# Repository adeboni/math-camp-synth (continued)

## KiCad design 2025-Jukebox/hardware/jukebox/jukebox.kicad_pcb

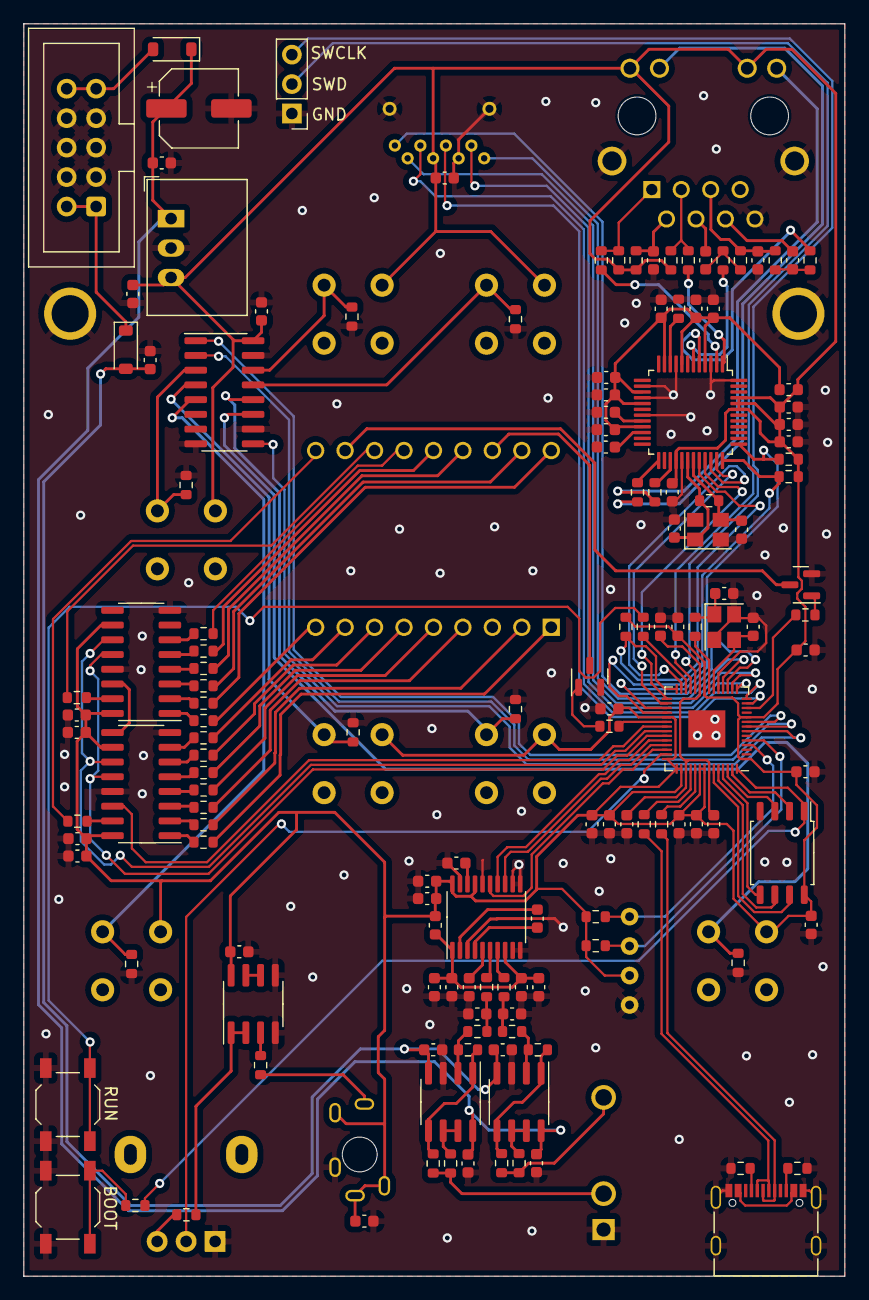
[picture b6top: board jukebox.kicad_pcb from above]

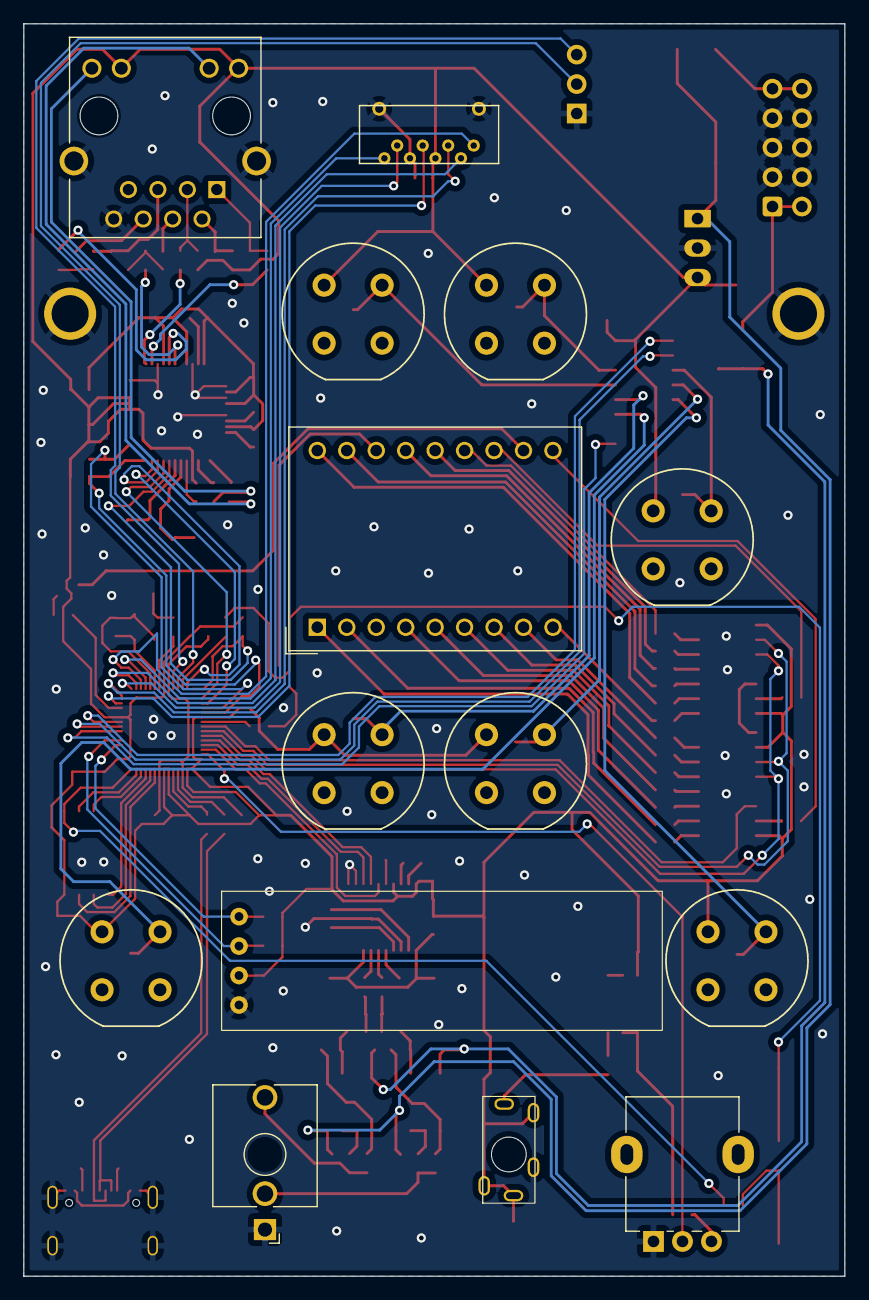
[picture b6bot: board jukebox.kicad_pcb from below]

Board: 2 copper layers, 70.8 x 108.0 mm, 160 parts (14 on the bottom side), 140 nets.

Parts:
C1, C2, C3, C4, C5, C6, C7, C8, C9, C13, C14, C15, C16, C17, C18, C19, C20, C21, C22, C23, C27, C31, C38, C40, C45, C46, C53, C54, C55, C56, C57, C59: 100n; C_0603_1608Metric
C10, C11, C44: 1u; C_0603_1608Metric
C12, C30, C36, C37, C39, C41, C42, C47, C48, C52, C58: 10u; C_0603_1608Metric
C24, C28: 27p; C_0603_1608Metric
C25, C29: 22p; C_0603_1608Metric
C26, C32: 10n; C_0603_1608Metric
C33, C34: 6.8n; C_0603_1608Metric
C35: 100u; CP_Elec_6.3x5.4
C43, C49: 2.2u; C_0603_1608Metric
C50, C51: 2.2n; C_0603_1608Metric
D1, D2: SM4007; D_SOD-123
FB1, FB3: FerriteBead; L_0603_1608Metric
H1, H2: MountingHole_Pad; MountingHole_3.2mm_M3_DIN965_Pad
J1: AudioJack3_SwitchTR; STX-3790-5N
J2: USB_C_Receptacle_USB2.0; USB_C_Receptacle_Palconn_UTC16-G
J3: AudioJack2_SwitchT; Jack_3.5mm_QingPu_WQP-PJ398SM_Vertical_CircularHoles
J4: SI-46001-F; BEL_SI-46001-F
J5: Conn_01x04; SSD1306
J6: Conn_02x05_Odd_Even; IDC-Header_2x05_P2.54mm_Vertical
J7: Conn_01x03; PinHeader_1x03_P2.54mm_Vertical
Q1, Q2: MMBT3904; SOT-23
R1, R2, R24, R25, R38: 1k; R_0603_1608Metric
R3, R6, R13, R17, R18, R28, R31, R32, R33, R35, R36, R37, R39, R40, R41, R58: 100; R_0603_1608Metric
R4, R5: 27; R_0603_1608Metric
R7, R10, R59, R61: 5.1k; R_0603_1608Metric
R8, R14, R16, R43, R44, R45, R46, R47, R48, R49, R50, R51, R54, R55: 10k; R_0603_1608Metric
R9, R11, R12, R15: 4.7; R_0603_1608Metric
R19, R20, R21, R22: 49.9; R_0603_1608Metric
R23: 1M; R_0603_1608Metric
R26, R27, R34, R42: 470; R_0603_1608Metric
R29: 12.4k; R_0603_1608Metric
R30: 10; R_0603_1608Metric
R52, R53, R56, R57: 75; R_0603_1608Metric
R60: 100k; R_0603_1608Metric
RV1: 100k; Potentiometer_Alpha_RD901F-40-00D_Single_Vertical
SW1, SW2: SW_Push; SW_SPST_TL3342
SW3, SW4, SW5, SW6, SW7, SW8, SW9: SW_Push; Push_E-Switch_KS01Q01
U1: PCM5100A; TSSOP-20_4.4x6.5mm_P0.65mm
U2: RP2040; QFN-56-1EP_7x7mm_P0.4mm_EP3.2x3.2mm
U3: W5500; LQFP-48_7x7mm_P0.5mm
U4: PDC54-11GWA; DA56-11CGKWA
U5, U8: 74HC595; SOIC-16_3.9x9.9mm_P1.27mm
U6: R-783.3-1.0; Converter_DCDC_RECOM_R-78E-0.5_THT
U7: W25Q128JVS; SOIC-8_5.23x5.23mm_P1.27mm
U9: PJS008U-3000-0
U10, U11: NE5532; SOIC-8_3.9x4.9mm_P1.27mm
U12: MCP6002-xSN; SOIC-8_3.9x4.9mm_P1.27mm
U13: 74HC165; SOIC-16_3.9x9.9mm_P1.27mm
Y1: 12MHz; Crystal_SMD_3225-4Pin_3.2x2.5mm
Y2: 25MHz; Crystal_SMD_3225-4Pin_3.2x2.5mm

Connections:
+1V1: C1.1, C2.1, C10.1, U2.23 (DVDD), U2.45 (VREG_VOUT), U2.50 (DVDD)
+3.3V: C3.1, C4.1, C5.1, C6.1, C7.1, C8.1, C9.1, C11.1, C12.1, C13.1, C14.1, C15.1, C16.1, C23.1, C27.1, C36.1, C37.1, C38.1, C39.1, C40.1, C42.1, C57.1, C58.1, C59.1, FB1.1, FB3.1, J1.R, J1.RN, J1.TN, J4.10, J4.12, J5.3, R8.1, R14.1, R16.1, R19.2, R20.2, R30.2, R59.2, R61.2, SW3.1, SW4.1, SW5.1, SW6.1, SW7.1, SW8.1, SW9.1, U1.17 (XSMT), U1.20 (DVDD), U2.1 (IOVDD), U2.10 (IOVDD), U2.22 (IOVDD), U2.33 (IOVDD), U2.42 (IOVDD), U2.43 (ADC_AVDD), U2.44 (VREG_IN), U2.48 (USB_VDD), U2.49 (IOVDD), U3.28 (VDD), U3.43 (PMODE2), U3.44 (PMODE1), U3.45 (PMODE0), U5.10 (~SRCLR), U5.16 (VCC), U6.3 (OUT), U7.8 (VCC), U8.10 (~SRCLR), U8.16 (VCC), U9.P$4 (4_VDD), U12.8 (V+), U13.16 (VCC)
+3.3VA: C17.1, C18.1, C19.1, C20.1, C21.1, C22.1, FB1.2, U3.4 (AVDD), U3.8 (AVDD), U3.11 (AVDD), U3.15 (AVDD), U3.17 (AVDD), U3.21 (AVDD)
+12V: C35.1, C41.1, C53.1, C55.1, D2.1 (K), U6.1 (IN), U10.8 (V+), U11.8 (V+)
-12V: C52.1, C54.2, C56.2, D1.2 (A), U10.4 (V-), U11.4 (V-)
/CS_0: R8.2, U2.28 (GPIO17), U3.32 (~SCS)
/INTn: R14.2, U2.32 (GPIO21), U3.36 (~INT)
/MISO_0: U2.27 (GPIO16), U3.34 (MISO)
/MOSI_0: U2.30 (GPIO19), U3.35 (MOSI)
/QSPI_SCLK: U2.52 (QSPI_SCLK), U7.6 (CLK)
/QSPI_SD0: U2.53 (QSPI_SD0), U7.5 (DI(IO0))
/QSPI_SD1: U2.55 (QSPI_SD1), U7.2 (DO(IO1))
/QSPI_SD2: U2.54 (QSPI_SD2), U7.3 (IO2)
/QSPI_SD3: U2.51 (QSPI_SD3), U7.7 (IO3)
/QSPI_SS: R38.1, U2.56 (QSPI_SS), U7.1 (~CS)
/RSTn: R16.2, U2.31 (GPIO20), U3.37 (~RST)
/RUN: R25.1, U2.26 (RUN)
/SCK_0: U2.29 (GPIO18), U3.33 (SCLK)
/~USB_BOOT: R38.2, SW2.2
ACTn: R27.1, U3.27 (ACTLED)
BCK_PWM1: U1.13 (BCK), U2.39 (GPIO27_ADC1)
BTN_CP: U2.8 (GPIO6), U13.2 (CP)
BTN_PL: U2.9 (GPIO7), U13.1 (~PL)
BTN_Q7: U2.7 (GPIO5), U13.9 (Q7)
D+: J2.A6 (D+), J2.B6 (D+), R4.1
D-: J2.A7 (D-), J2.B7 (D-), R5.1
GND: C1.2, C2.2, C3.2, C4.2, C5.2, C6.2, C7.2, C8.2, C9.2, C10.2, C11.2, C12.2, C13.2, C14.2, C15.2, C16.2, C17.2, C18.2, C19.2, C20.2, C21.2, C22.2, C23.2, C24.2, C25.1, C26.1, C27.2, C28.2, C29.2, C30.2, C31.2, C32.1, C35.2, C36.2, C37.2, C38.2, C39.2, C40.2, C41.2, C42.2, C44.2, C45.2, C46.2, C47.2, C48.2, C49.2, C50.2, C51.1, C52.2, C53.2, C54.1, C55.2, C56.1, C57.2, C58.2, C59.2, H1.1, H2.1, J1.S, J2.A1 (GND), J2.A12 (GND), J2.B1 (GND), J2.B12 (GND), J2.S1 (SHIELD), J3.S, J4.8, J4.SH, J5.4, J6.3, J6.4, J6.5, J6.6, J6.7, J6.8, J7.1, Q1.2 (E), Q2.2 (E), R7.1, R10.1, R29.1, R43.2, R44.2, R45.2, R46.2, R47.2, R48.2, R49.2, RV1.1, SW1.1, SW2.1, U1.3 (CPGND), U1.9 (AGND), U1.10 (DEMP), U1.11 (FLT), U1.12 (SCK), U1.16 (FMT), U1.19 (DGND), U2.19 (TESTEN), U2.57 (GND), U3.3 (AGND), U3.9 (AGND), U3.14 (AGND), U3.16 (AGND), U3.19 (AGND), U3.29 (GND), U3.48 (AGND), U5.8 (GND), U5.13 (~OE), U6.2 (GND), U7.4 (GND), U8.8 (GND), U8.13 (~OE), U9.P$6 (6_VSS/GND), U9.P$9 (HOUSING_1), U9.P$10 (HOUSING_2), U10.3 (+), U11.3 (+), U12.4 (V-), U12.5 (+), U13.8 (GND), U13.10 (DS), U13.15 (~CE), Y1.2, Y1.4, Y2.2, Y2.4
LINKn: R26.1, U3.25 (LINKLED)
LRCLK_PWM0: U1.15 (LRCK), U2.40 (GPIO28_ADC2)
NUM_A: R33.1, U4.12 (A)
NUM_B: R3.1, U4.10 (B)
NUM_C: R35.1, U4.9 (C)
NUM_D: R31.1, U4.7 (D)
NUM_DIG1: R1.2, U2.34 (GPIO22)
NUM_DIG2: R2.2, U2.12 (GPIO9)
NUM_DP: R32.1, U4.8 (DP)
NUM_E: R6.1, U4.1 (E)
NUM_EN: U2.37 (GPIO25), U5.12 (RCLK), U8.12 (RCLK)
NUM_F: R36.1, U4.18 (F)
NUM_G: R37.1, U4.17 (G)
NUM_H: R39.1, U4.15 (H)
NUM_J: R40.1, U4.14 (J)
NUM_K: R28.1, U4.6 (K)
NUM_L: R18.1, U4.5 (L)
NUM_M: R17.1, U4.4 (M)
NUM_N: R13.1, U4.2 (N)
NUM_P: R41.1, U4.13
NUM_SCK: U2.36 (GPIO24), U5.11 (SRCLK), U8.11 (SRCLK)
NUM_SER: U2.35 (GPIO23), U5.14 (SER)
unnamed: C28.1, R24.2, Y1.1
unnamed: C50.1, R42.2, R55.1
unnamed: C51.2, R34.2, R50.1
unnamed: D1.1 (K), J6.1, J6.2
unnamed: D2.2 (A), J6.9, J6.10
unnamed: J1.T, R60.1
unnamed: J2.A5 (CC1), R7.2
unnamed: J2.B5 (CC2), R10.2
unnamed: J2.A4 (VBUS), J2.A9 (VBUS), J2.B4 (VBUS), J2.B9 (VBUS)
unnamed: J3.T, R56.2, R57.2
unnamed: J3.TN, R52.2, R53.2
unnamed: J4.9, R27.2
unnamed: J4.11, R26.2
unnamed: C33.2, J4.4 (RD+)
unnamed: C34.1, J4.6 (RD-)
unnamed: C32.2, J4.2 (TCT), R30.1
unnamed: J7.2, U2.25 (SWD)
unnamed: J7.3, U2.24 (SWCLK)
unnamed: Q1.1 (B), R1.1
unnamed: Q1.3 (C), U4.16 (DIG_1)
unnamed: Q2.1 (B), R2.1
unnamed: Q2.3 (C), U4.11 (DIG_2)
unnamed: R25.2, SW1.2
unnamed: R58.2, RV1.3
unnamed: C43.2, U1.4 (CAPM)
unnamed: C43.1, U1.2 (CAPP)
unnamed: C44.1, U1.18 (LDOO)
unnamed: R34.1, U1.6 (OUTL)
unnamed: R42.1, U1.7 (OUTR)
unnamed: C49.1, U1.5 (VNEG)
unnamed: R5.2, U2.46 (USB_DM)
unnamed: R4.2, U2.47 (USB_DP)
unnamed: C24.1, U2.20 (XIN), Y1.3
unnamed: R24.1, U2.21 (XOUT)
unnamed: C31.1, U3.22 (1V2O)
unnamed: R29.2, U3.10 (EXRES1)
unnamed: R12.1, U3.5 (RXN)
unnamed: R15.2, U3.6 (RXP)
unnamed: C30.1, U3.20 (TOCAP)
unnamed: R9.1, U3.1 (TXN)
unnamed: R11.2, U3.2 (TXP)
unnamed: C25.2, R23.2, U3.30 (XI/CLKIN), Y2.1
unnamed: C29.1, R23.1, U3.31 (XO), Y2.3
unnamed: R3.2, U5.15 (QA)
unnamed: R6.2, U5.1 (QB)
unnamed: R13.2, U5.2 (QC)
unnamed: R17.2, U5.3 (QD)
unnamed: R18.2, U5.4 (QE)
unnamed: R28.2, U5.5 (QF)
unnamed: R31.2, U5.6 (QG)
unnamed: U5.9 (QH'), U8.14 (SER)
unnamed: R32.2, U5.7 (QH)
unnamed: R33.2, U8.15 (QA)
unnamed: R35.2, U8.1 (QB)
unnamed: R36.2, U8.2 (QC)
unnamed: R37.2, U8.3 (QD)
unnamed: R39.2, U8.4 (QE)
unnamed: R40.2, U8.5 (QF)
unnamed: R41.2, U8.6 (QG)
unnamed: R50.2, R51.1, U10.2 (-)
unnamed: R51.2, R53.1, U10.1, U10.5 (+)
unnamed: R52.1, U10.6 (-), U10.7
unnamed: R54.1, R55.2, U11.2 (-)
unnamed: R54.2, R57.1, U11.1, U11.5 (+)
unnamed: R56.1, U11.6 (-), U11.7
unnamed: R60.2, U12.3 (+)
unnamed: R58.1, U12.1, U12.2 (-)
unnamed: U12.6 (-), U12.7
unnamed: R49.1, SW3.2, U13.11 (D0)
unnamed: R48.1, SW6.2, U13.12 (D1)
unnamed: R47.1, SW4.2, U13.13 (D2)
unnamed: R46.1, SW5.2, U13.14 (D3)
unnamed: R45.1, SW8.2, U13.3 (D4)
unnamed: R44.1, SW7.2, U13.4 (D5)
unnamed: R43.1, SW9.2, U13.5 (D6)
PCM_DATA: U1.14 (DIN), U2.38 (GPIO26_ADC0)
RCT: C26.2, J4.5 (RCT), R21.2, R22.2
RXN: C34.2, R12.2, R21.1
RXP: C33.1, R15.1, R22.1
SCL: J5.2, R61.1, U2.5 (GPIO3)
SDA: J5.1, R59.1, U2.4 (GPIO2)
SD_CLK: U2.13 (GPIO10), U9.P$5 (5_CLK)
SD_CMD: U2.14 (GPIO11), U9.P$3 (3_CMD/DI)
SD_DAT0: U2.15 (GPIO12), U9.P$7 (7_DAT0/D0)
SD_DAT1: U2.18 (GPIO15), U9.P$8 (8_DAT1/X)
SD_DAT2: U2.17 (GPIO14), U9.P$1 (1_DAT2/X)
SD_DAT3: U2.16 (GPIO13), U9.P$2 (2_CD/DAT3/CS)
TXN: J4.3 (TD-), R9.2, R19.1
TXP: J4.1 (TD+), R11.1, R20.1
VOLUME: RV1.2, U2.41 (GPIO29_ADC3)
V_AUDIO: C45.1, C46.1, C47.1, C48.1, FB3.2, U1.1 (CPVDD), U1.8 (AVDD)

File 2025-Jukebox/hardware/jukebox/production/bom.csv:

Designator,Footprint,Quantity,Value,LCSC Part #
"C1, C13, C14, C15, C16, C17, C18, C19, C2, C20, C21, C22, C23, C27, C3, C31, C38, C4, C40, C45, C46, C5, C53, C54, C55, C56, C57, C59, C6, C7, C8, C9",0603,32,100n,C14663
"C10, C11, C44",0603,3,1u,C15849
"C12, C30, C36, C37, C39, C41, C42, C47, C48, C52, C58",0603,11,10u,C96446
"C24, C28",0603,2,27p,C1653
"C25, C29",0603,2,22p,C1653
"C26, C32",0603,2,10n,C57112
"C33, C34",0603,2,6.8n,C1631
C35,CP_Elec_6.3x5.4,1,100u,C180946
"C43, C49",0603,2,2.2u,C23630
"C50, C51",0603,2,2.2n,C1604
"D1, D2",D_SOD-123,2,SM4007,C64898
"FB1, FB3",0603,2,FerriteBead,C1002
J2,USB_C_Receptacle_Palconn_UTC16-G,1,USB_C_Receptacle_USB2.0,C709357
"Q1, Q2",SOT-23,2,MMBT3904,C20526
"R1, R2, R24, R25, R38",0603,5,1k,C21190
"R10, R59, R61, R7",0603,4,5.1k,C23186
"R11, R12, R15, R9",0603,4,4.7,C23164
"R13, R17, R18, R28, R3, R31, R32, R33, R35, R36, R37, R39, R40, R41, R58, R6",0603,16,100,C22775
"R14, R16, R43, R44, R45, R46, R47, R48, R49, R50, R51, R54, R55, R8",0603,14,10k,C25804
"R19, R20, R21, R22",0603,4,49.9,C23185
R23,0603,1,1M,C22935
"R26, R27, R34, R42",0603,4,470,C23179
R29,0603,1,12.4k,C22865
R30,0603,1,10,C22859
"R4, R5",0603,2,27,C25190
"R52, R53, R56, R57",0603,4,75,C4275
R60,0603,1,100k,C25803
"SW1, SW2",SW_SPST_TL3342,2,SW_Push,C318884
U1,TSSOP-20_4.4x6.5mm_P0.65mm,1,PCM5100A,C107671
"U10, U11",SOIC-8_3.9x4.9mm_P1.27mm,2,NE5532,C7426
U12,SOIC-8_3.9x4.9mm_P1.27mm,1,MCP6002-xSN,C7377
U13,SOIC-16_3.9x9.9mm_P1.27mm,1,74HC165,C5613
U2,QFN-56-1EP_7x7mm_P0.4mm_EP3.2x3.2mm,1,RP2040,C2040
U3,LQFP-48_7x7mm_P0.5mm,1,W5500,C32843
"U5, U8",SOIC-16_3.9x9.9mm_P1.27mm,2,74HC595,C5947
U7,SOIC-8_5.23x5.23mm_P1.27mm,1,W25Q128JVS,C97521
Y1,Crystal_SMD_3225-4Pin_3.2x2.5mm,1,12MHz,C9002
Y2,Crystal_SMD_3225-4Pin_3.2x2.5mm,1,25MHz,C9006

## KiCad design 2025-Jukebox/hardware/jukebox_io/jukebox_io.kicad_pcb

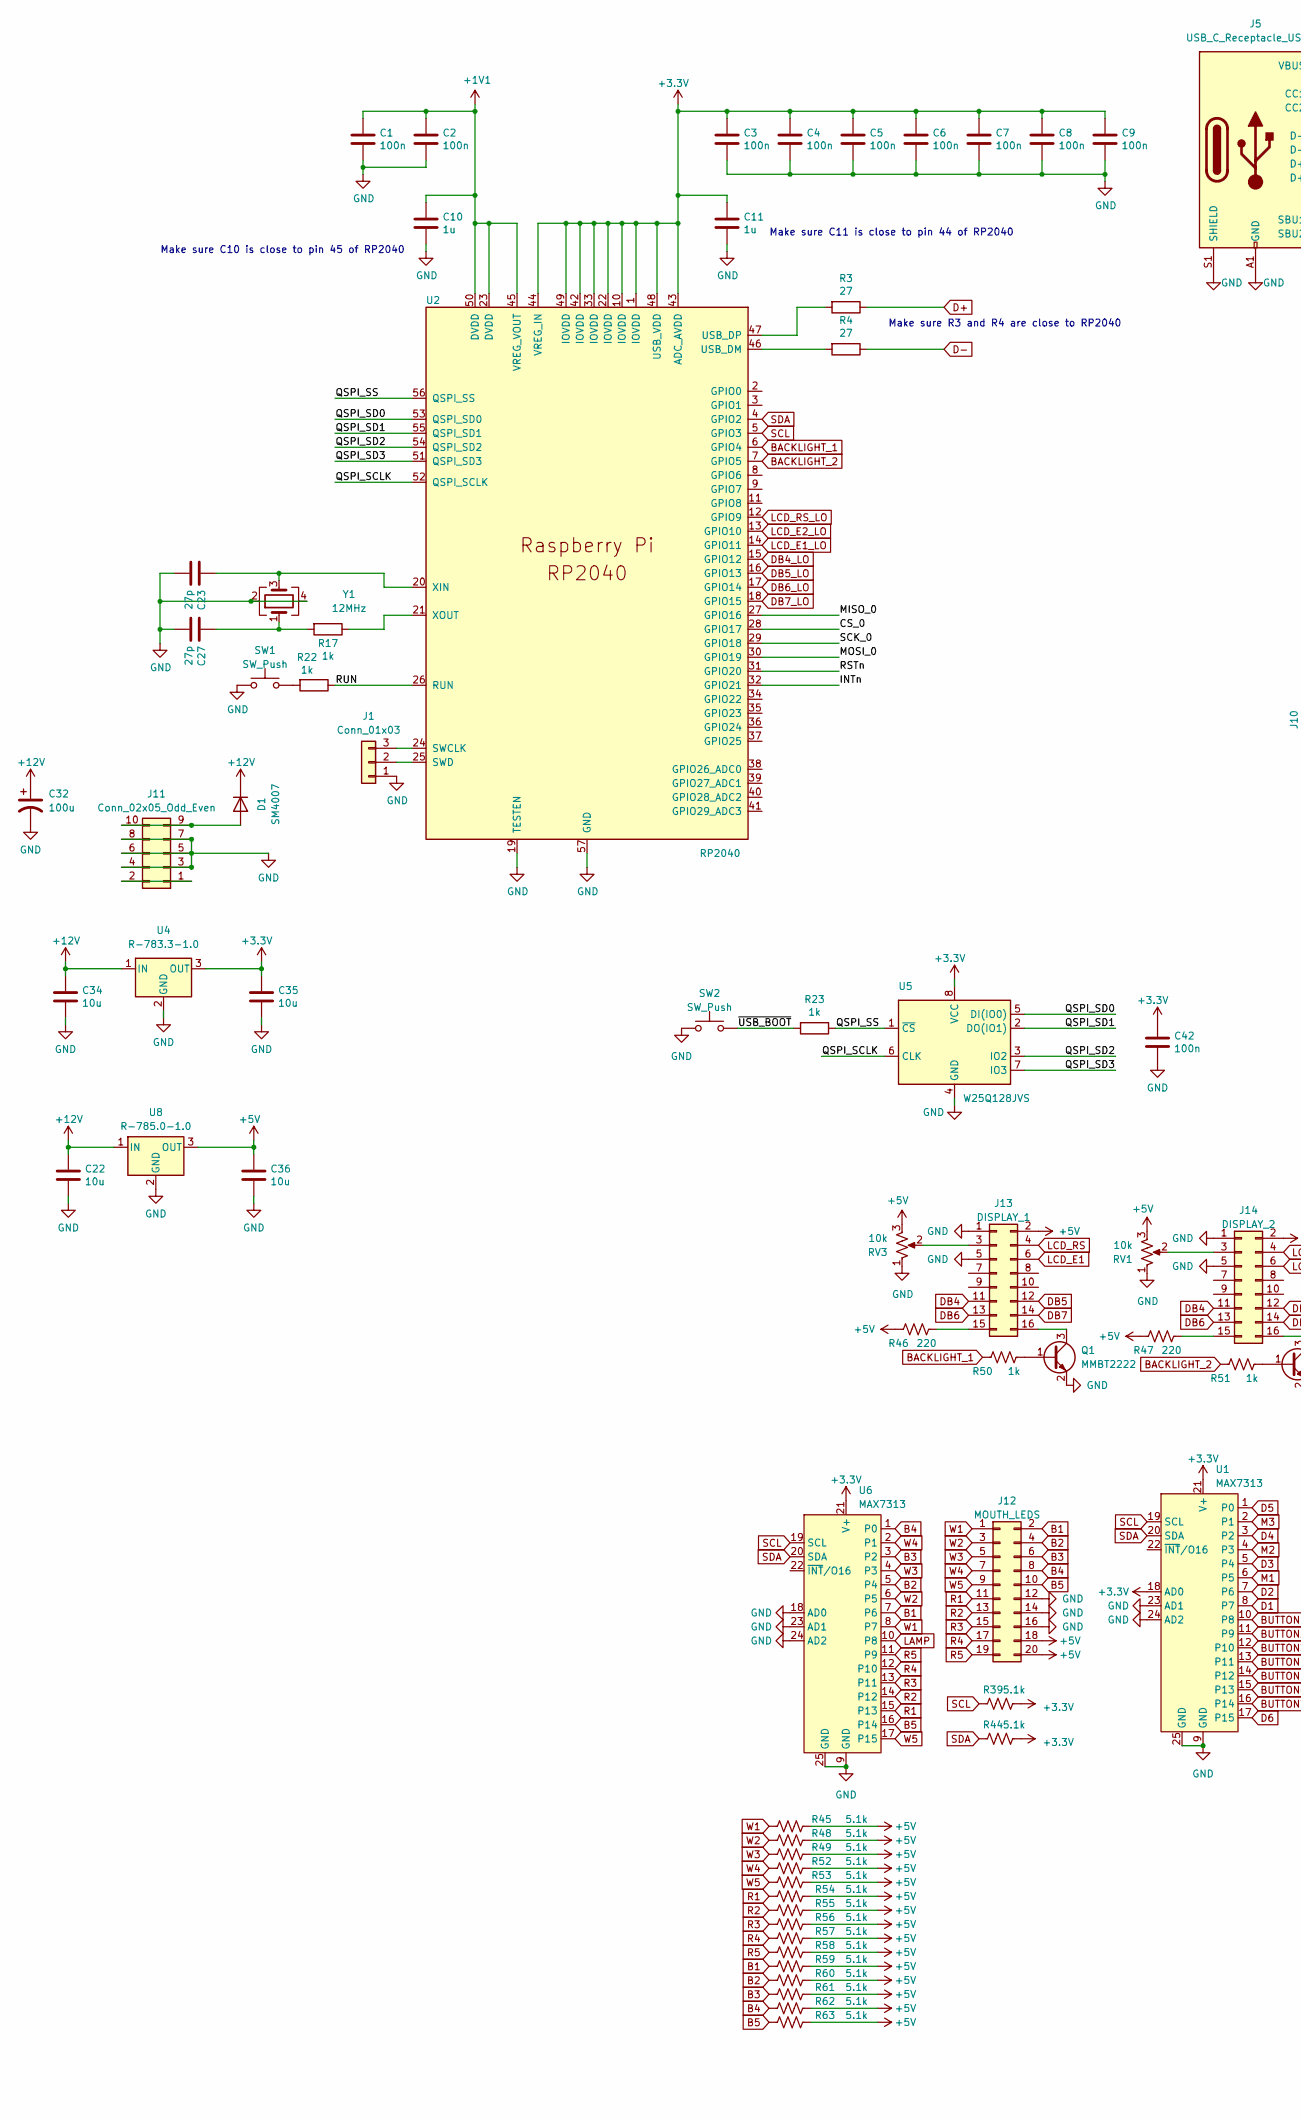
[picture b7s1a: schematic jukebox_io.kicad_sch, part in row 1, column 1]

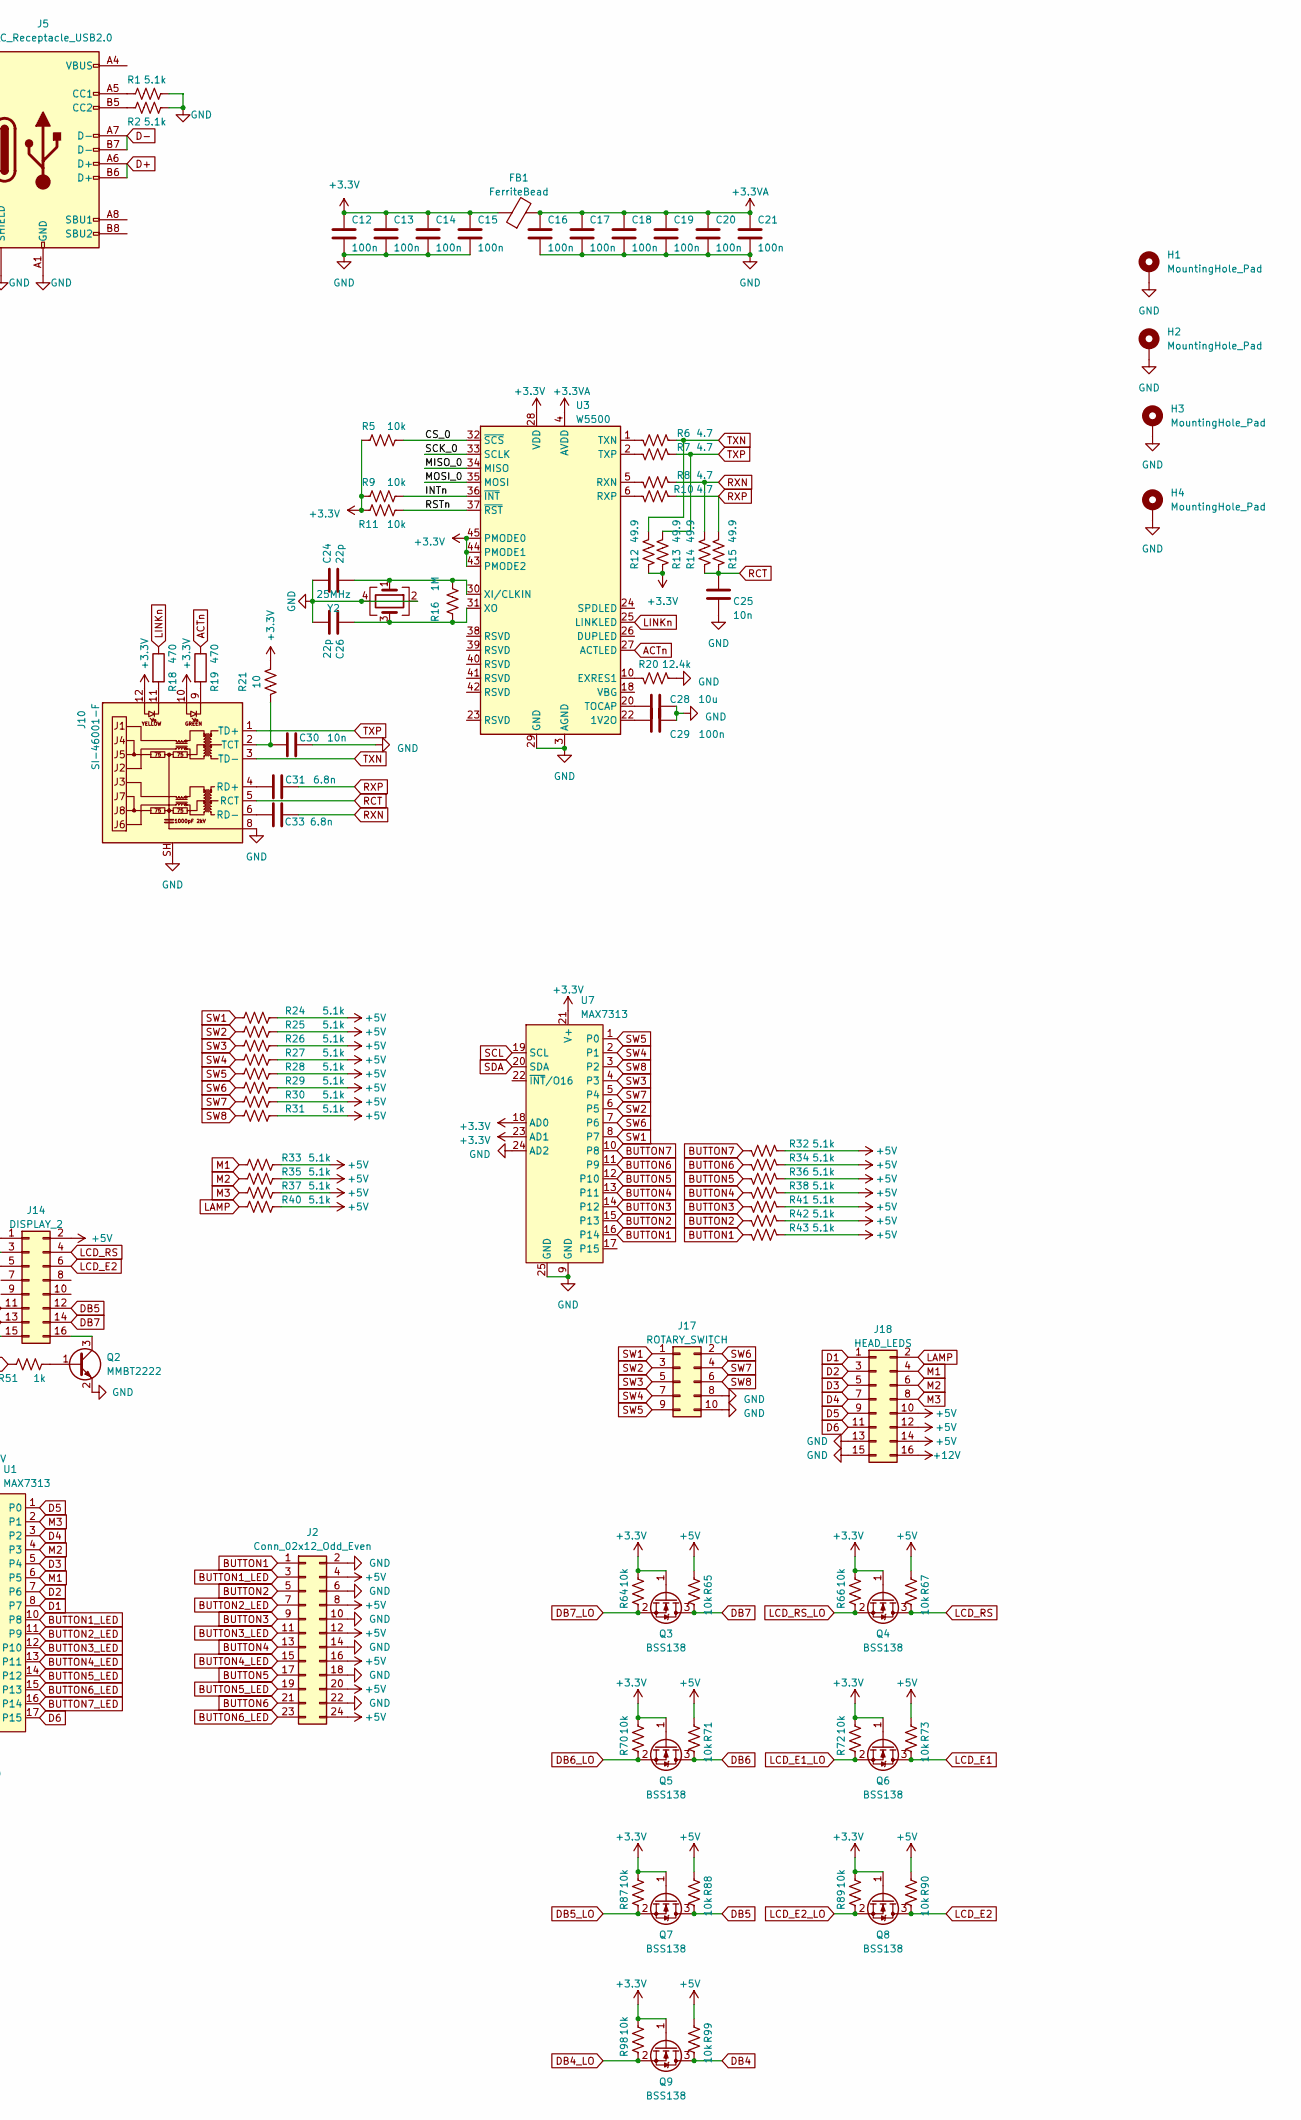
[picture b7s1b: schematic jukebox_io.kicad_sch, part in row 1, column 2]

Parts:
C1, C2, C3, C4, C5, C6, C7, C8, C9, C12, C13, C14, C15, C16, C17, C18, C19, C20, C21, C29, C42: 100n; C_0603_1608Metric
C10, C11: 1u; C_0603_1608Metric
C22, C28, C34, C35, C36: 10u; C_0603_1608Metric
C23, C27: 27p; C_0603_1608Metric
C24, C26: 22p; C_0603_1608Metric
C25, C30: 10n; C_0603_1608Metric
C31, C33: 6.8n; C_0603_1608Metric
C32: 100u; CP_Elec_6.3x5.4
D1: SM4007; D_SOD-123
FB1: FerriteBead; L_0603_1608Metric
H1, H2, H3, H4: MountingHole_Pad; MountingHole_3.2mm_M3_DIN965_Pad
J1: Conn_01x03; PinHeader_1x03_P2.54mm_Vertical
J2: Conn_02x12_Odd_Even; IDC-Header_2x12_P2.54mm_Vertical
J5: USB_C_Receptacle_USB2.0; USB_C_Receptacle_Palconn_UTC16-G
J10: SI-46001-F; BEL_SI-46001-F
J11: Conn_02x05_Odd_Even; IDC-Header_2x05_P2.54mm_Vertical
J12: MOUTH_LEDS; IDC-Header_2x10_P2.54mm_Vertical
J13: DISPLAY_1; IDC-Header_2x08_P2.54mm_Vertical
J14: DISPLAY_2; IDC-Header_2x08_P2.54mm_Vertical
J17: ROTARY_SWITCH; IDC-Header_2x05_P2.54mm_Vertical
J18: HEAD_LEDS; IDC-Header_2x08_P2.54mm_Vertical
Q1, Q2: MMBT2222; SOT-23
Q3, Q4, Q5, Q6, Q7, Q8, Q9: BSS138; SOT-23
R1, R2, R24, R25, R26, R27, R28, R29, R30, R31, R32, R33, R34, R35, R36, R37, R38, R39, R40, R41, R42, R43, R44, R45, R48, R49, R52, R53, R54, R55, R56, R57, R58, R59, R60, R61, R62, R63: 5.1k; R_0603_1608Metric
R3, R4: 27; R_0603_1608Metric
R5, R9, R11, R64, R65, R66, R67, R70, R71, R72, R73, R87, R88, R89, R90, R98, R99: 10k; R_0603_1608Metric
R6, R7, R8, R10: 4.7; R_0603_1608Metric
R12, R13, R14, R15: 49.9; R_0603_1608Metric
R16: 1M; R_0603_1608Metric
R17, R22, R23, R50, R51: 1k; R_0603_1608Metric
R18, R19: 470; R_0603_1608Metric
R20: 12.4k; R_0603_1608Metric
R21: 10; R_0603_1608Metric
R46, R47: 220; R_0603_1608Metric
RV1, RV3: 10k; Potentiometer_Bourns_3296W_Vertical
SW1, SW2: SW_Push; SW_SPST_TL3342
U1, U6, U7: MAX7313; TQFN-24-1EP_4x4mm_P0.5mm_EP2.6x2.6mm_ThermalVias
U2: RP2040; QFN-56-1EP_7x7mm_P0.4mm_EP3.2x3.2mm
U3: W5500; LQFP-48_7x7mm_P0.5mm
U4: R-783.3-1.0; Converter_DCDC_RECOM_R-78E-0.5_THT
U5: W25Q128JVS; SOIC-8_5.23x5.23mm_P1.27mm
U8: R-785.0-1.0; Converter_DCDC_RECOM_R-78E-0.5_THT
Y1: 12MHz; Crystal_SMD_3225-4Pin_3.2x2.5mm
Y2: 25MHz; Crystal_SMD_3225-4Pin_3.2x2.5mm

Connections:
+1V1: C1.1, C2.1, C10.1, U2.23 (DVDD), U2.45 (VREG_VOUT), U2.50 (DVDD)
+3.3V: C3.1, C4.1, C5.1, C6.1, C7.1, C8.1, C9.1, C11.1, C12.1, C13.1, C14.1, C15.1, C35.1, C42.1, FB1.1, J10.10, J10.12, Q3.1 (G), Q4.1 (G), Q5.1 (G), Q6.1 (G), Q7.1 (G), Q8.1 (G), Q9.1 (G), R5.1, R9.1, R11.1, R12.2, R13.2, R21.2, R39.2, R44.2, R64.2, R66.2, R70.2, R72.2, R87.2, R89.2, R98.2, U1.18 (AD0), U1.21 (V+), U2.1 (IOVDD), U2.10 (IOVDD), U2.22 (IOVDD), U2.33 (IOVDD), U2.42 (IOVDD), U2.43 (ADC_AVDD), U2.44 (VREG_IN), U2.48 (USB_VDD), U2.49 (IOVDD), U3.28 (VDD), U3.43 (PMODE2), U3.44 (PMODE1), U3.45 (PMODE0), U4.3 (OUT), U5.8 (VCC), U6.21 (V+), U7.18 (AD0), U7.21 (V+), U7.23 (AD1)
+3.3VA: C16.1, C17.1, C18.1, C19.1, C20.1, C21.1, FB1.2, U3.4 (AVDD), U3.8 (AVDD), U3.11 (AVDD), U3.15 (AVDD), U3.17 (AVDD), U3.21 (AVDD)
+5V: C36.1, J2.4, J2.8, J2.12, J2.16, J2.20, J2.24, J12.18, J12.20, J13.2, J14.2, J18.10, J18.12, J18.14, R24.2, R25.2, R26.2, R27.2, R28.2, R29.2, R30.2, R31.2, R32.2, R33.2, R34.2, R35.2, R36.2, R37.2, R38.2, R40.2, R41.2, R42.2, R43.2, R45.2, R46.1, R47.1, R48.2, R49.2, R52.2, R53.2, R54.2, R55.2, R56.2, R57.2, R58.2, R59.2, R60.2, R61.2, R62.2, R63.2, R65.1, R67.1, R71.1, R73.1, R88.1, R90.1, R99.1, RV1.3, RV3.3, U8.3 (OUT)
+12V: C22.1, C32.1, C34.1, D1.1 (K), J18.16, U4.1 (IN), U8.1 (IN)
/CS_0: R5.2, U2.28 (GPIO17), U3.32 (~SCS)
/INTn: R9.2, U2.32 (GPIO21), U3.36 (~INT)
/MISO_0: U2.27 (GPIO16), U3.34 (MISO)
/MOSI_0: U2.30 (GPIO19), U3.35 (MOSI)
/QSPI_SCLK: U2.52 (QSPI_SCLK), U5.6 (CLK)
/QSPI_SD0: U2.53 (QSPI_SD0), U5.5 (DI(IO0))
/QSPI_SD1: U2.55 (QSPI_SD1), U5.2 (DO(IO1))
/QSPI_SD2: U2.54 (QSPI_SD2), U5.3 (IO2)
/QSPI_SD3: U2.51 (QSPI_SD3), U5.7 (IO3)
/QSPI_SS: R23.1, U2.56 (QSPI_SS), U5.1 (~CS)
/RSTn: R11.2, U2.31 (GPIO20), U3.37 (~RST)
/RUN: R22.1, U2.26 (RUN)
/SCK_0: U2.29 (GPIO18), U3.33 (SCLK)
/~USB_BOOT: R23.2, SW2.2
ACTn: R19.1, U3.27 (ACTLED)
B1: J12.2, R59.1, U6.7 (P6)
B2: J12.4, R60.1, U6.5 (P4)
B3: J12.6, R61.1, U6.3 (P2)
B4: J12.8, R62.1, U6.1 (P0)
B5: J12.10, R63.1, U6.16 (P14)
BACKLIGHT_1: R50.1, U2.6 (GPIO4)
BACKLIGHT_2: R51.1, U2.7 (GPIO5)
BUTTON1: J2.1, R43.1, U7.16 (P14)
BUTTON1_LED: J2.3, U1.10 (P8)
BUTTON2: J2.5, R42.1, U7.15 (P13)
BUTTON2_LED: J2.7, U1.11 (P9)
BUTTON3: J2.9, R41.1, U7.14 (P12)
BUTTON3_LED: J2.11, U1.12 (P10)
BUTTON4: J2.13, R38.1, U7.13 (P11)
BUTTON4_LED: J2.15, U1.13 (P11)
BUTTON5: J2.17, R36.1, U7.12 (P10)
BUTTON5_LED: J2.19, U1.14 (P12)
BUTTON6: J2.21, R34.1, U7.11 (P9)
BUTTON6_LED: J2.23, U1.15 (P13)
BUTTON7: R32.1, U7.10 (P8)
BUTTON7_LED: U1.16 (P14)
D1: J18.1, U1.8 (P7)
D2: J18.3, U1.7 (P6)
D3: J18.5, U1.5 (P4)
D4: J18.7, U1.3 (P2)
D5: J18.9, U1.1 (P0)
D6: J18.11, U1.17 (P15)
D+: J5.A6 (D+), J5.B6 (D+), R3.1
D-: J5.A7 (D-), J5.B7 (D-), R4.1
DB4: J13.11, J14.11, Q9.3 (D), R99.2
DB4_LO: Q9.2 (S), R98.1, U2.15 (GPIO12)
DB5: J13.12, J14.12, Q7.3 (D), R88.2
DB5_LO: Q7.2 (S), R87.1, U2.16 (GPIO13)
DB6: J13.13, J14.13, Q5.3 (D), R71.2
DB6_LO: Q5.2 (S), R70.1, U2.17 (GPIO14)
DB7: J13.14, J14.14, Q3.3 (D), R65.2
DB7_LO: Q3.2 (S), R64.1, U2.18 (GPIO15)
GND: C1.2, C2.2, C3.2, C4.2, C5.2, C6.2, C7.2, C8.2, C9.2, C10.2, C11.2, C12.2, C13.2, C14.2, C15.2, C16.2, C17.2, C18.2, C19.2, C20.2, C21.2, C22.2, C23.2, C24.1, C25.1, C26.2, C27.2, C28.2, C29.2, C30.1, C32.2, C34.2, C35.2, C36.2, C42.2, H1.1, H2.1, H3.1, H4.1, J1.1, J2.2, J2.6, J2.10, J2.14, J2.18, J2.22, J5.A1 (GND), J5.A12 (GND), J5.B1 (GND), J5.B12 (GND), J5.S1 (SHIELD), J10.8, J10.SH, J11.3, J11.4, J11.5, J11.6, J11.7, J11.8, J12.12, J12.14, J12.16, J13.1, J13.5, J14.1, J14.5, J17.8, J17.10, J18.13, J18.15, Q1.2 (E), Q2.2 (E), R1.1, R2.1, R20.1, RV1.1, RV3.1, SW1.1, SW2.1, U1.9 (GND), U1.23 (AD1), U1.24 (AD2), U1.25 (GND), U2.19 (TESTEN), U2.57 (GND), U3.3 (AGND), U3.9 (AGND), U3.14 (AGND), U3.16 (AGND), U3.19 (AGND), U3.29 (GND), U3.48 (AGND), U4.2 (GND), U5.4 (GND), U6.9 (GND), U6.18 (AD0), U6.23 (AD1), U6.24 (AD2), U6.25 (GND), U7.9 (GND), U7.24 (AD2), U7.25 (GND), U8.2 (GND), Y1.2, Y1.4, Y2.2, Y2.4
LAMP: J18.2, R40.1, U6.10 (P8)
LCD_E1: J13.6, Q6.3 (D), R73.2
LCD_E1_LO: Q6.2 (S), R72.1, U2.14 (GPIO11)
LCD_E2: J14.6, Q8.3 (D), R90.2
LCD_E2_LO: Q8.2 (S), R89.1, U2.13 (GPIO10)
LCD_RS: J13.4, J14.4, Q4.3 (D), R67.2
LCD_RS_LO: Q4.2 (S), R66.1, U2.12 (GPIO9)
LINKn: R18.1, U3.25 (LINKLED)
M1: J18.4, R33.1, U1.6 (P5)
M2: J18.6, R35.1, U1.4 (P3)
M3: J18.8, R37.1, U1.2 (P1)
unnamed: C27.1, R17.2, Y1.1
unnamed: D1.2 (A), J11.9, J11.10
unnamed: J1.2, U2.25 (SWD)
unnamed: J1.3, U2.24 (SWCLK)
unnamed: J5.A5 (CC1), R1.2
unnamed: J5.B5 (CC2), R2.2
unnamed: J5.A4 (VBUS), J5.A9 (VBUS), J5.B4 (VBUS), J5.B9 (VBUS)
unnamed: J10.9, R19.2
unnamed: J10.11, R18.2
unnamed: C31.2, J10.4 (RD+)
unnamed: C33.1, J10.6 (RD-)
unnamed: C30.2, J10.2 (TCT), R21.1
unnamed: J11.1, J11.2
unnamed: J13.3, RV3.2
unnamed: J13.15, R46.2
unnamed: J13.16, Q1.3 (C)
unnamed: J14.3, RV1.2
unnamed: J14.15, R47.2
unnamed: J14.16, Q2.3 (C)
unnamed: Q1.1 (B), R50.2
unnamed: Q2.1 (B), R51.2
unnamed: R22.2, SW1.2
unnamed: R4.2, U2.46 (USB_DM)
unnamed: R3.2, U2.47 (USB_DP)
unnamed: C23.1, U2.20 (XIN), Y1.3
unnamed: R17.1, U2.21 (XOUT)
unnamed: C29.1, U3.22 (1V2O)
unnamed: R20.2, U3.10 (EXRES1)
unnamed: R8.1, U3.5 (RXN)
unnamed: R10.2, U3.6 (RXP)
unnamed: C28.1, U3.20 (TOCAP)
unnamed: R6.1, U3.1 (TXN)
unnamed: R7.2, U3.2 (TXP)
unnamed: C24.2, R16.2, U3.30 (XI/CLKIN), Y2.1
unnamed: C26.1, R16.1, U3.31 (XO), Y2.3
R1: J12.11, R54.1, U6.15 (P13)
R2: J12.13, R55.1, U6.14 (P12)
R3: J12.15, R56.1, U6.13 (P11)
R4: J12.17, R57.1, U6.12 (P10)
R5: J12.19, R58.1, U6.11 (P9)
RCT: C25.2, J10.5 (RCT), R14.2, R15.2
RXN: C33.2, R8.2, R14.1
RXP: C31.1, R10.1, R15.1
SCL: R39.1, U1.19 (SCL), U2.5 (GPIO3), U6.19 (SCL), U7.19 (SCL)
SDA: R44.1, U1.20 (SDA), U2.4 (GPIO2), U6.20 (SDA), U7.20 (SDA)
SW1: J17.1, R24.1, U7.8 (P7)
SW2: J17.3, R25.1, U7.6 (P5)
SW3: J17.5, R26.1, U7.4 (P3)
SW4: J17.7, R27.1, U7.2 (P1)
SW5: J17.9, R28.1, U7.1 (P0)
SW6: J17.2, R29.1, U7.7 (P6)
SW7: J17.4, R30.1, U7.5 (P4)
SW8: J17.6, R31.1, U7.3 (P2)
TXN: J10.3 (TD-), R6.2, R12.1
TXP: J10.1 (TD+), R7.1, R13.1
W1: J12.1, R45.1, U6.8 (P7)
W2: J12.3, R48.1, U6.6 (P5)
W3: J12.5, R49.1, U6.4 (P3)
W4: J12.7, R52.1, U6.2 (P1)
W5: J12.9, R53.1, U6.17 (P15)

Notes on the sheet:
Make sure C11 is close to pin 44 of RP2040
Make sure R3 and R4 are close to RP2040
Make sure C10 is close to pin 45 of RP2040

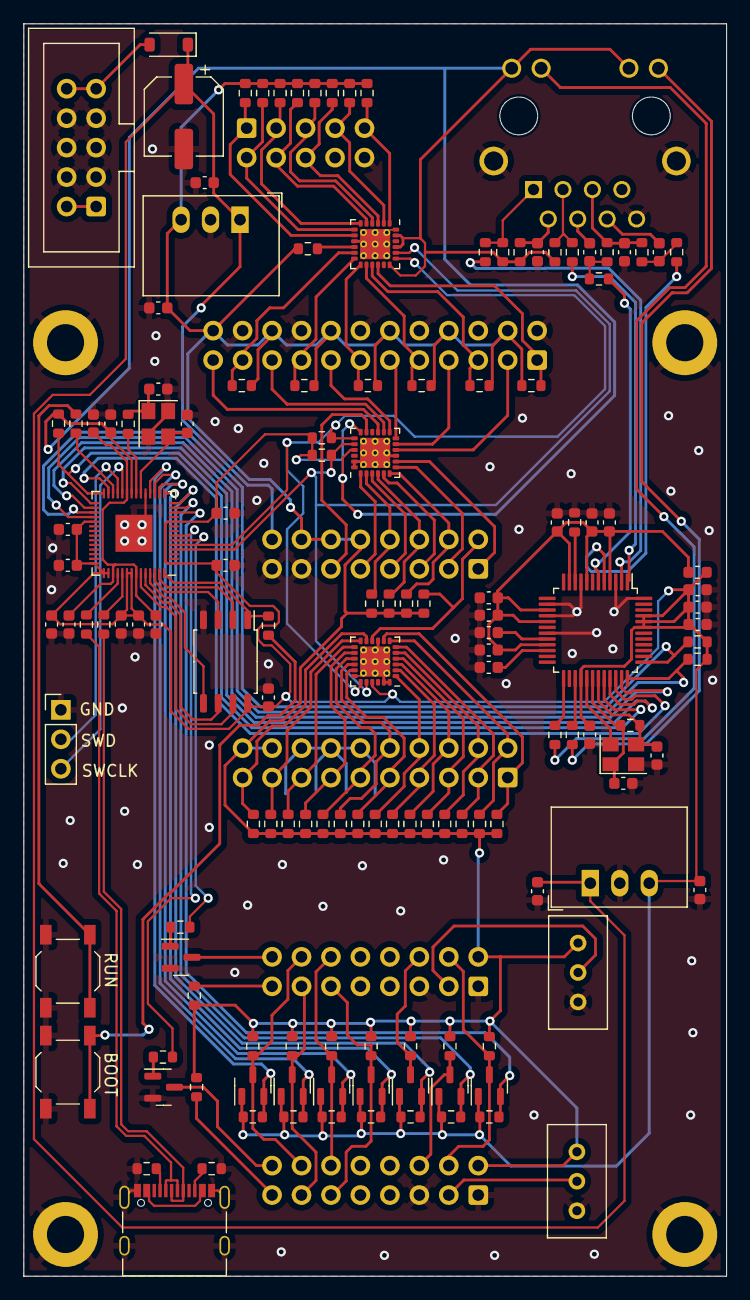
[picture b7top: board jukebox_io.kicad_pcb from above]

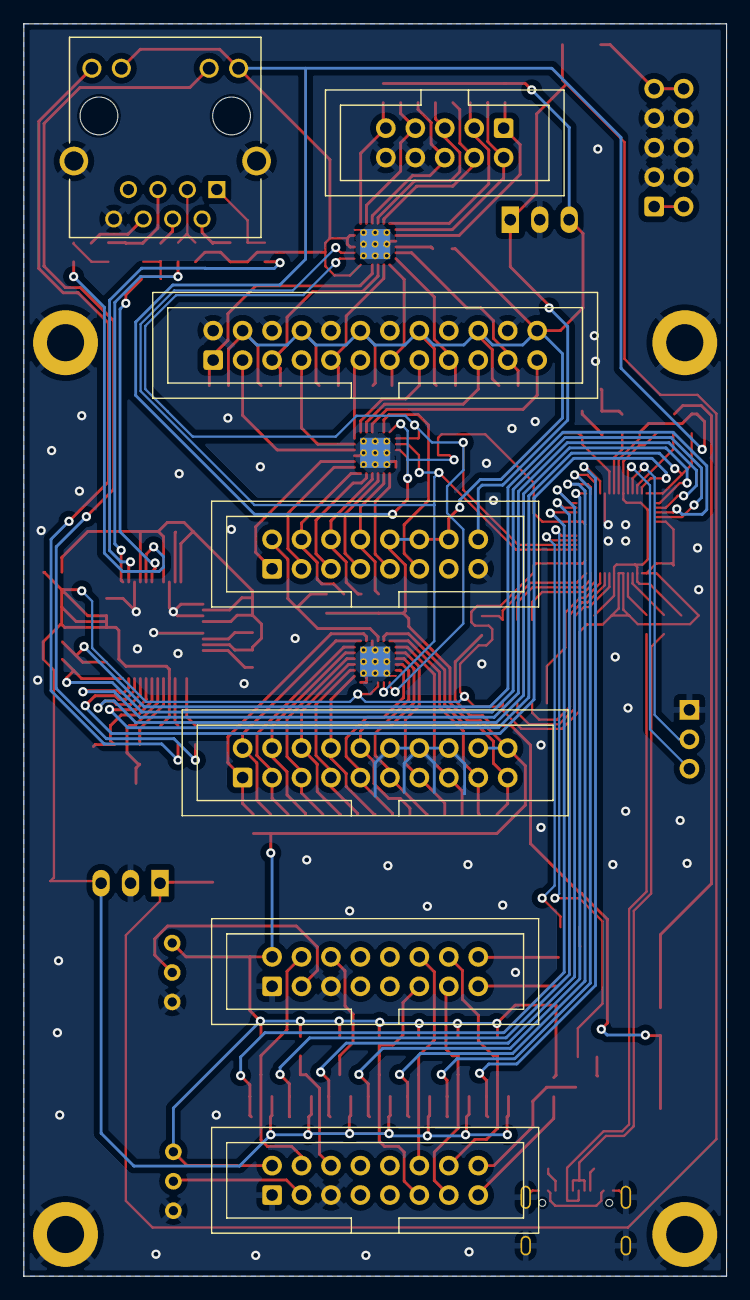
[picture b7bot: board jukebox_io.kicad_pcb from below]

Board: 2 copper layers, 60.6 x 108.0 mm, 153 parts (7 on the bottom side), 128 nets.

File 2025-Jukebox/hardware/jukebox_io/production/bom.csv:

Designator,Footprint,Quantity,Value,LCSC Part #
"C1, C12, C13, C14, C15, C16, C17, C18, C19, C2, C20, C21, C29, C3, C4, C42, C5, C6, C7, C8, C9",0603,21,100n,C14663
"C10, C11",0603,2,1u,C15849
"C22, C28, C34, C35, C36",0603,5,10u,C96446
"C23, C27",0603,2,27p,C1653
"C24, C26",0603,2,22p,C1653
"C25, C30",0603,2,10n,C57112
"C31, C33",0603,2,6.8n,C1631
C32,CP_Elec_6.3x5.4,1,100u,C180946
D1,D_SOD-123,1,SM4007,C64898
FB1,0603,1,FerriteBead,C1002
J5,USB_C_Receptacle_Palconn_UTC16-G,1,USB_C_Receptacle_USB2.0,C709357
"Q1, Q2",SOT-23,2,MMBT2222,C8512
"Q3, Q4, Q5, Q6, Q7, Q8, Q9",SOT-23,7,BSS138,C7420339
"R1, R2, R24, R25, R26, R27, R28, R29, R30, R31, R32, R33, R34, R35, R36, R37, R38, R39, R40, R41, R42, R43, R44, R45, R48, R49, R52, R53, R54, R55, R56, R57, R58, R59, R60, R61, R62, R63",0603,38,5.1k,C23186
"R10, R6, R7, R8",0603,4,4.7,C23164
"R11, R5, R64, R65, R66, R67, R70, R71, R72, R73, R87, R88, R89, R9, R90, R98, R99",0603,17,10k,C25804
"R12, R13, R14, R15",0603,4,49.9,C23185
R16,0603,1,1M,C22935
"R17, R22, R23, R50, R51",0603,5,1k,C21190
"R18, R19",0603,2,470,C23179
R20,0603,1,12.4k,C22865
R21,0603,1,10,C22859
"R3, R4",0603,2,27,C25190
"R46, R47",0603,2,220,C22962
"SW1, SW2",SW_SPST_TL3342,2,SW_Push,C318884
"U1, U6, U7",TQFN-24-1EP_4x4mm_P0.5mm_EP2.6x2.6mm_ThermalVias,3,MAX7313,C2669657
U2,QFN-56-1EP_7x7mm_P0.4mm_EP3.2x3.2mm,1,RP2040,C2040
U3,LQFP-48_7x7mm_P0.5mm,1,W5500,C32843
U5,SOIC-8_5.23x5.23mm_P1.27mm,1,W25Q128JVS,C97521
Y1,Crystal_SMD_3225-4Pin_3.2x2.5mm,1,12MHz,C9002
Y2,Crystal_SMD_3225-4Pin_3.2x2.5mm,1,25MHz,C9006
